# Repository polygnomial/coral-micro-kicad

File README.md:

# Google Coral Micro KiCad files

- use altium2kicad to convert
- fix certain text fields
- fix schematic libraries
- link schematics hierarchicly
- put all rescued footprints in new footprint library
- delete all the random files

## TODO

- fix STEP files

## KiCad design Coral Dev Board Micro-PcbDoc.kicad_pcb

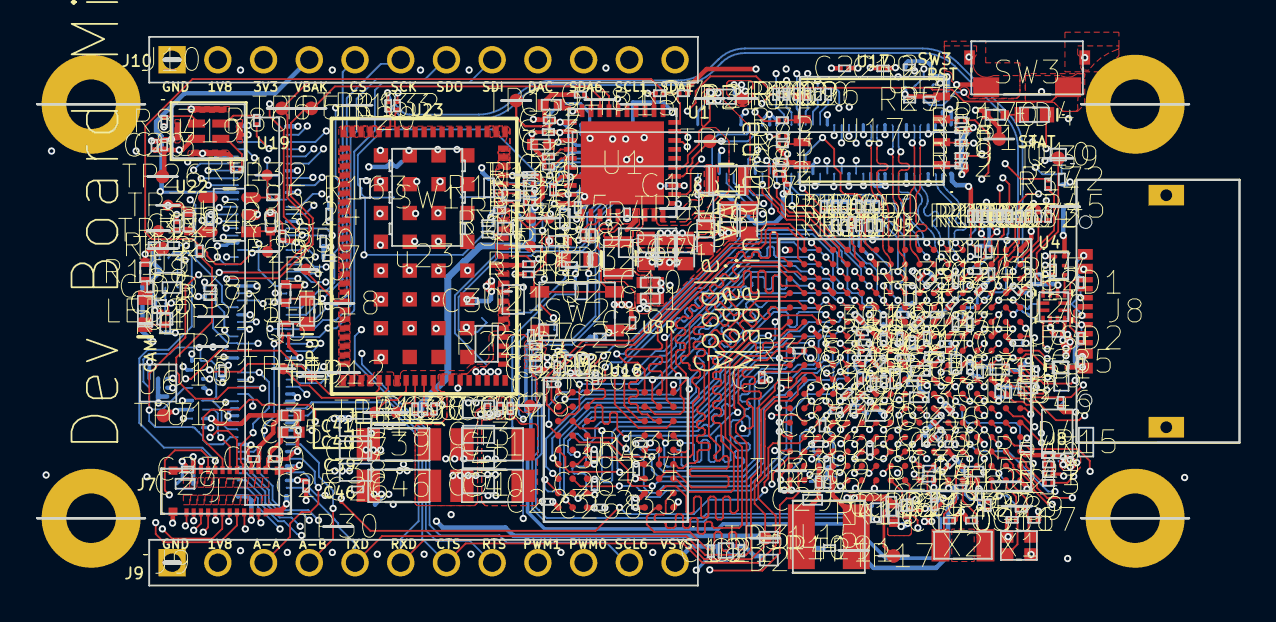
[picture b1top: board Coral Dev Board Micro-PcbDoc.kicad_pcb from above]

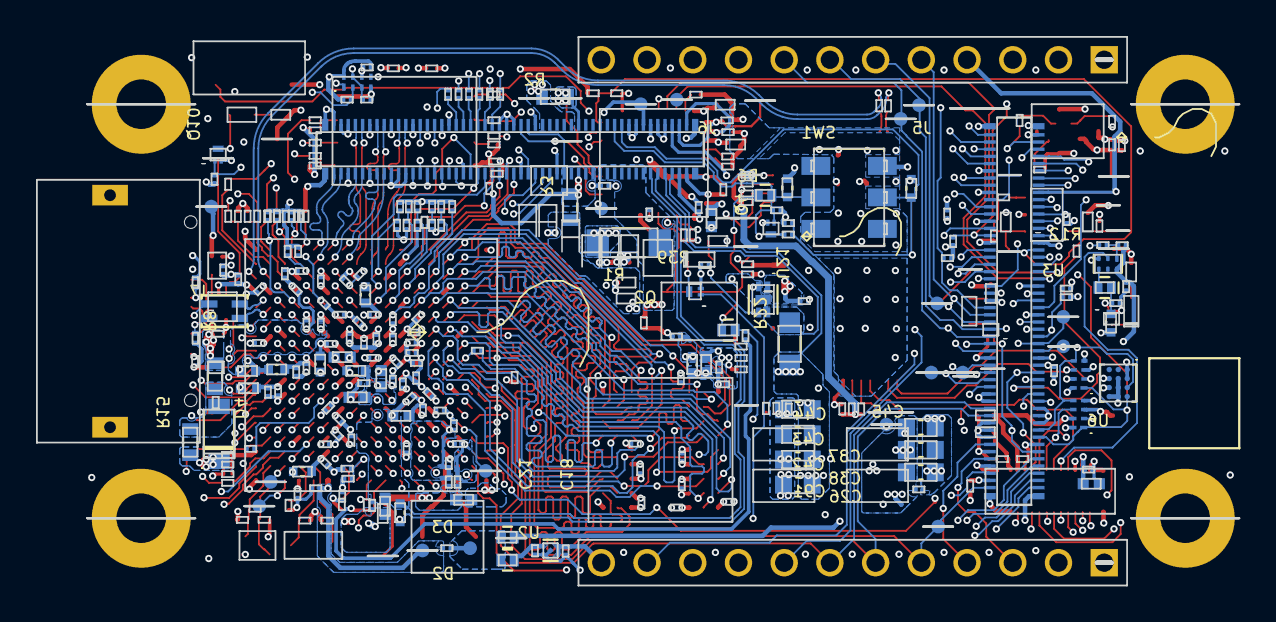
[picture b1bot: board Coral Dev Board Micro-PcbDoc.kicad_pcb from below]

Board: 8 copper layers, 66.8 x 30.5 mm, 356 parts (200 on the bottom side), 316 nets.

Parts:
C1: C1; C0201_MOD
C2: C2; C0402
C3: C3; C0402
C4: C4; C0603_L_ZEROMASK
C5: C5; C0603_L_ZEROMASK
C6: C6; C0603_L_ZEROMASK
C7: C7; C0603_L_ZEROMASK
C8: C8; C0603_L_ZEROMASK
C9: C9; C0603_L_ZEROMASK
C10: C10; C0402
C11: C11; C0402
C12: C12; C0201_MOD
C13: C13; C0201_MOD
C14: C14; C0201_MOD
C15: C15; C0201_MOD
C16: C16; C0201_MOD
C17: C17; C0201_MOD
C18: C18; C0201_MOD
C19: C19; C0201_MOD
C20: C20; C0201_MOD
C21: C21; C0201_MOD
C22: C22; C0201_MOD
C23: C23; C0201_MOD
C24: C24; C0201_MOD
C25: C25; C0201_MOD
C26: C26; C0201_MOD
C27: C27; C0201_MOD
C28: C28; C0201_MOD
C29: C29; C0402
C30: C30; C0201_MOD
C31: C31; C0402
C32: C32; C0402
C33: C33; C0201_MOD
C34: C34; C0201_MOD
C35: C35; C0402
C36: C36; C0201_MOD
C37: C37; C0201_MOD
C38: C38; C0603
C39: C39; C1206Y_1.90MM
C40: C40; C1206Y_1.90MM
C41: C41; C1206Y_1.90MM
C42: C42; C0603
C43: C43; C0603
C44: C44; C0603
C45: C45; C0603
C46: C46; C1206Y_1.90MM
C57: C57; C0201_MOD
C61: C61; C0402
C62: C62; C0201_MOD
C63: C63; C0402
C67: C67; C0201_MOD
C74: C74; C0402
C79: C79; C0201_MOD
C80: C80; C0201_MOD
C81: C81; C0201_MOD
C82: C82; C0201_MOD
C83: C83; C0201_MOD
C84: C84; C0201_MOD
C85: C85; C0201_MOD
C87: C87; C0603
C88: C88; C0201_MOD
C90: C90; C0201_MOD
C91: C91; C0603
C92: C92; C0201_MOD
C93: C93; C0201_MOD
C94: C94; C0201_MOD
C95: C95; C0201_MOD
C96: C96; C0201_MOD
C97: C97; C0201_MOD
C98: C98; C0201_MOD
C102: C102; C0201_MOD
C107: C107; C0201_MOD
C109: C109; C0201_MOD
C110: C110; C0201_MOD
C115: C115; C0201_MOD
C117: C117; C0201_MOD
C118: C118; C0402
C119: C119; C0201_MOD
C124: C124; C0201_MOD
C136: C136; C0201_MOD
C138: C138; C0402
C223: C223; C0201_MOD
C224: C224; C0201_MOD
C233: C233; C0201_MOD
C234: C234; C0201_MOD
C235: C235; C0201_MOD
C239: C239; C0201_MOD
C241: C241; C0201_MOD
C242: C242; C0201_MOD
C244: C244; C0201_MOD
C245: C245; C0201_MOD
C251: C251; C0201_MOD
C252: C252; C0201_MOD
C254: C254; C0201_MOD
C256: C256; C0201_MOD
C257: C257; C0201_MOD
C258: C258; C0201_MOD
C260: C260; C0201_MOD
C261: C261; C0201_MOD
C264: C264; C0201_MOD
C265: C265; C0201_MOD
C266: C266; C0201_MOD
C267: C267; C0201_MOD
C268: C268; C0201_MOD
C269: C269; C0201_MOD
C270: C270; C0201_MOD
C272: C272; C0201_MOD
C273: C273; C0201_MOD
C276: C276; C0201_MOD
C277: C277; C0201_MOD
C279: C279; C0201_MOD
C280: C280; C0201_MOD
C285: C285; C0201_MOD
C286: C286; C0201_MOD
C287: C287; C0201_MOD
C290: C290; C0201_MOD
C293: C293; C0201_MOD
C294: C294; C0402
C296: C296; C0201_MOD
C297: C297; C0402
C300: C300; C0201_MOD
C302: C302; C0201_MOD
C303: C303; C0201_MOD
C304: C304; C0201_MOD
C305: C305; C0201_MOD
C316: C316; C0201_MOD
C317: C317; C0201_MOD
C327: C327; C0201_MOD
C345: C345; C0201_MOD
C347: C347; C0201_MOD
C348: C348; C0201_MOD
D1: D1; D0402_H0.55MM
D2: D2; D0402_H0.55MM
D3: D3; D0402_H0.55MM
D4: D4; SOD123_AK
D5: D5; D0402_H0.55MM
D6: D6; D0402_H0.55MM
D31: D31; SOD1060X40
ESD1: ESD1; 0201
ESD2: ESD2; 0201
FB1: FB1; L0402_H0.55MM
FB2: FB2; L0402_H0.55MM
FB3: FB3; L0402_H0.55MM
FB4: FB4; L0402_H0.55MM
FB5: FB5; L0402_H0.55MM
FB6: FB6; L0402_H0.55MM
J5: J5; HIROSE_DF40C-100DP-0.4V(51)
J6: J6; HIROSE_DF40C-100DP-0.4V(51)
J7: J7; Molex_5037722410_HM01B0
J8: J8; EDAC_698B116W26A-661
J9: J9; HEADER_1X12_POS_UNSHROUDED
J10: J10; HEADER_1X12_POS_UNSHROUDED
L1: L1; L2016_H1.0MM
L2: L2; L2016_H1.0MM
L7: L7; IND4_CHOKE_0805
L15: L15; IND_74404041047
LED2: LED2; LED_0603_0.67mm
LED3: LED3; LED_0603_0.67mm
LED4: LED4; LED_0603P_ORANGE
LED5: LED5; LED_0603P_WHITE
Q1: Q1; 3XDFN
Q2: Q2; 3XDFN
Q3: Q3; 3XDFN
Q4: Q4; 3XDFN
Q10: Q10; 3XDFN
R1: R1; R1206
R2: R2; R0603
R3: R3; R0603
R4: R4; R0201_MOD
R5: R5; R0201_MOD
R6: R6; R0201_MOD
R7: R7; R0201_MOD
R8: R8; R0603
R9: R9; R0201_MOD
R10: R10; R0201_MOD
R11: R11; R0402
R12: R12; R0201_MOD
R13: R13; R0201_MOD
R14: R14; R0201_MOD
R15: R15; R0603
R16: R16; R0201_MOD
R17: R17; R0201_MOD
R18: R18; R0201_MOD
R19: R19; R0201_MOD
R20: R20; R0201_MOD
R21: R21; R0201_MOD
R22: R22; R0805
R23: R23; R0201_MOD
R24: R24; R0201_MOD
R26: R26; R0201_MOD
R27: R27; R0201_MOD
R29: R29; R0201_MOD
R30: R30; R0201_MOD
R31: R31; R0201_MOD
R32: R32; R0201_MOD
R33: R33; R0201_MOD
R34: R34; R0201_MOD
R35: R35; R0201_MOD
R36: R36; R0201_MOD
R37: R37; R0201_MOD
R38: R38; R0201_MOD
R39: R39; R0201_MOD
R40: R40; R0201_MOD
R41: R41; R0201_MOD
R43: R43; R0201_MOD
R44: R44; R0201_MOD
R45: R45; R0201_MOD
R46: R46; R0201_MOD
R47: R47; R0201_MOD
R48: R48; R0201_MOD
R49: R49; R0201_MOD
R50: R50; R0201_MOD
R51: R51; R0201_MOD
R53: R53; R0201_MOD
R71: R71; R0201_MOD
R72: R72; R0201_MOD
R73: R73; R0201_MOD
R74: R74; R0201_MOD
R75: R75; R0201_MOD
R76: R76; R0201_MOD
R78: R78; R0201_MOD
R79: R79; R0201_MOD
R84: R84; R0201_MOD
R85: R85; R0201_MOD
R86: R86; R0201_MOD
R87: R87; R0201_MOD
R90: R90; R0201_MOD
R91: R91; R0201_MOD
R93: R93; R0402
R95: R95; R0201_MOD
R99: R99; R0402
R110: R110; R0201_MOD
R116: R116; R0201_MOD
R117: R117; R0402
R125: R125; R0201_MOD
R129: R129; R0201_MOD
R132: R132; R0201_MOD
R133: R133; R0201_MOD
R135: R135; R0201_MOD
R136: R136; R0201_MOD
R137: R137; R0201_MOD
R138: R138; R0201_MOD
R139: R139; R0201_MOD
R140: R140; R0201_MOD
R141: R141; R0201_MOD
R142: R142; R0201_MOD
R143: R143; R0201_MOD
R144: R144; R0201_MOD
R145: R145; R0201_MOD
R146: R146; R0201_MOD
R147: R147; R0201_MOD
R148: R148; R0201_MOD
R149: R149; R0201_MOD
R150: R150; R0201_MOD
R151: R151; R0201_MOD
R152: R152; R0201_MOD
R153: R153; R0201_MOD
R154: R154; R0201_MOD
R155: R155; R0201_MOD
R156: R156; R0201_MOD
R157: R157; R0201_MOD
R158: R158; R0201_MOD
R159: R159; R0201_MOD
R160: R160; R0201_MOD
R161: R161; R0201_MOD
R162: R162; R0201_MOD
R163: R163; R0402
R164: R164; R0402
R166: R166; R0201_MOD
R167: R167; R0201_MOD
R168: R168; R0402
R169: R169; R0402
R170: R170; R0402
R171: R171; R0402
R172: R172; R0201_MOD
R189: R189; R0201_MOD
R194: R194; R0402
R215: R215; R0201_MOD
R365: R365; R0201_MOD
R373: R373; R0201_MOD
R374: R374; R0201_MOD
R375: R375; R0201_MOD
R396: R396; R0201_MOD
R397: R397; R0201_MOD
R398: R398; R0201_MOD
R415: R415; R0402
R416: R416; R0402
R419: R419; R0201_MOD
R1821: R1821; R0201_MOD
R1848: R1848; R0201_MOD
SW1: SW1; SWITCH_CAS-D20TA
SW2: SW2; SWITCH_TAH1QR
SW3: SW3; SWITCH_TL4100AF120QG
TP1: TP1; TESTPAD_SMT_30MIL
TP2: TP2; TESTPAD_SMT_30MIL
TP3: TP3; TESTPAD_SMT_30MIL
TP4: TP4; TESTPAD_SMT_30MIL
TP5: TP5; TESTPAD_SMT_30MIL
TP6: TP6; TESTPAD_SMT_30MIL
TP7: TP7; TESTPAD_SMT_30MIL
TP8: TP8; TESTPAD_SMT_30MIL
TP9: TP9; TESTPAD_SMT_30MIL
TP10: TP10; TESTPAD_SMT_30MIL
TP11: TP11; TESTPAD_SMT_30MIL
TP12: TP12; TESTPAD_SMT_30MIL
TP13: TP13; TESTPAD_SMT_30MIL
TP14: TP14; TESTPAD_SMT_30MIL
TP15: TP15; TESTPAD_SMT_30MIL
TP16: TP16; TESTPAD_SMT_30MIL
TP17: TP17; TESTPAD_SMT_30MIL
TP18: TP18; TESTPAD_SMT_30MIL
TP19: TP19; TESTPAD_SMT_30MIL
TP20: TP20; TESTPAD_SMT_30MIL
TP21: TP21; TESTPAD_SMT_30MIL
TP22: TP22; TESTPAD_SMT_30MIL
TP23: TP23; TESTPAD_SMT_30MIL
TP24: TP24; TESTPAD_SMT_30MIL
TP25: TP25; TESTPAD_SMT_30MIL
TP26: TP26; TESTPAD_SMT_30MIL
TP27: TP27; TESTPAD_SMT_30MIL
TP28: TP28; TESTPAD_SMT_25MIL
TP29: TP29; TESTPAD_SMT_25MIL
TP30: TP30; TESTPAD_SMT_30MIL
TP31: TP31; TESTPAD_SMT_30MIL
TP32: TP32; TESTPAD_SMT_25MIL
TP33: TP33; TESTPAD_SMT_25MIL
TP34: TP34; TESTPAD_SMT_25MIL
TP35: TP35; TESTPAD_SMT_25MIL
TP36: TP36; TESTPAD_SMT_25MIL
TP37: TP37; TESTPAD_SMT_25MIL
TP38: TP38; TESTPAD_SMT_25MIL
TP39: TP39; TESTPAD_SMT_30MIL
TP40: TP40; TESTPAD_SMT_25MIL
TP41: TP41; TESTPAD_SMT_25MIL
TP42: TP42; TESTPAD_SMT_25MIL
TP43: TP43; TESTPAD_SMT_25MIL
TP44: TP44; TESTPAD_SMT_25MIL
TP45: TP45; TESTPAD_SMT_30MIL
U1: U1; QFN50P600X600X90-40-TP
U2: U2; SDFN80X80X40-5
U3: U3; SON50P145X100X60-6
U4: U4; SON50P145X100X50-6
U5: U5; BGA289C80P17X17_1400X14000X152
U6: U6; BGA12C50+3X4_206X202X65
U10: U10; SON8_0P5_1L95x1W
U13: U13; SON8_0P5_1L95x1W
U14: U14; SON8_0P5_1L95x1W
U17: U17; UDFN800X600X65-8
U18: U18; BGA54C80P6X9_800X800X100
U19: U19; MIC_SPK0641HT4H-1
U20: U20; X2QFN12_1.6X1.6MMM
U21: U21; TDFN120X160X60-4-TP
U22: U22; 5SOT23_REG
X1: X1; XTAL_MURATA_XRCGB24M000F1H01R0
X2: X2; XTAL_EPSON_ADUCM355BCCZ
u23: u23; QFN120_0P5_10X15

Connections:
ADC1_CH0A: J5.10, J9.3, U5.N13
ADC1_CH0B: J5.14, J9.4, U5.T17
ADC1_CH2A: C33.1, R40.1, R41.2, U5.R17
ADC1_CH2B: J5.6, U5.P16
ADC_1V8_IN: C117.1, C136.1, C347.1, C348.1, FB2.2, U5.G16, U5.K15, U5.M11
BOOT_MODE0: J6.19, R30.1, R31.2, R163.2, SW1.5, U5.P6
BOOT_MODE1: D6.A, J6.21, Q4.1, R29.1, R164.2, SW1.2, U5.T7
BRD_STAT_LED: J5.80, Q10.1, R172.1, U5.L9
BT_CFG1_0_ENET_RGMII_TXD3: R10.2, R139.1, R151.1, U5.D10
BT_CFG1_1_ENET_RGMII_TXD2: R16.2, R140.1, R152.1, U5.E12
BT_CFG1_2_ENET_RGMII_TXD1: R18.2, R141.1, R153.1, U5.A15
BT_CFG1_3_ENET_RGMII_TXD0: R19.2, R142.1, R154.1, U5.C13
BT_CFG1_4_ENET_RGMII_TX_EN: R20.2, R143.1, R155.1, U5.B14
BT_CFG1_5_ENET_RGMII_TXC: R26.2, R144.1, R156.1, U5.A14
BT_CFG1_6: R145.1, R157.1, U5.E8
BT_CFG1_7: R146.1, R158.1, U5.F8
BT_CFG2_0: R147.1, R159.1, U5.E9
BT_CFG2_1: R148.1, R160.1, U5.D7
BT_CFG2_2: R149.1, R161.1, U5.C7
BT_CFG2_3: R150.1, R162.1, U5.C9
BT_CFG_IO_EN: R27.2, U5.P13, U14.3, U14.7
BT_DEV_WAKE: J6.62, U5.A7
BT_HOST_WAKE: J6.50, U5.A4
BT_REG_ON: J5.87, U5.G17
BUCK2_SW: L1.1, U1.20
BUCK3_SW: L2.1, U1.17
CAMERA_INT: J5.33, J7.9, U5.P9
CAMERA_TRIG: J7.4, U5.T2
CON_DET: TP39.1, U20.5
CRYPTO_RST_N: U5.U8, U6.C3
CSI_DATA02: J7.17, U5.J12
CSI_DATA03: J7.18, U5.K12
CSI_DATA04: J7.19, U5.K14
CSI_DATA05: J7.20, U5.K13
CSI_DATA06: J7.21, U5.L16
CSI_DATA07: J7.22, U5.M16
CSI_DATA08: J7.23, U5.N15
CSI_DATA09: J7.24, U5.N17
CSI_HSYNC: J7.6, U5.M14
CSI_MCLK: J7.14, R44.2
CSI_MCLK_RT: R44.1, U5.L12
CSI_PIXCLK: J7.16, U5.P17
CSI_VSYNC: J7.5, U3.2, U5.N14
DAC_OUT: D31.K, J5.95, J10.9, U5.H16
DA_GPIO0_WDOG_KICK: J5.55, TP27.1, U1.21, U5.P10
DA_GPIO2: J5.63, U1.28
DA_GPIO3: J5.65, U1.29
DA_GPIO4_SYS_EN: J5.67, R6.2, R7.1, R9.2, U1.30
DA_IREF: R5.2, U1.4
DA_VDDCORE: C1.2, U1.39
DA_VREF: C16.1, U1.5
DA_nIRQ: J5.61, TP6.1, U1.37
DA_nONKEY: D1.K, D6.K, R166.1, SW2.1, SW2.2, U1.15
DA_nRESET: J5.59, TP5.1, U1.38
DA_nRESETREQ: J5.74, R4.1, U1.16
DCDC_1V8_OUT: C19.1, C22.1, C279.1, FB2.1, J6.10, R7.2, R23.2, R24.2, R139.2, R140.2, R141.2, R142.2, R143.2, R144.2, R145.2, R146.2, R147.2, R148.2, R149.2, R150.2, R373.2, R374.2, R416.2, SW1.4, U5.M6
DCDC_1V8_OUT_SENSE: C118.1, C124.1, C138.1, C280.1, J6.12, R416.1, U5.M7, U5.M8
DCDC_PSWITCH: C286.1, R396.2, U5.P3
DMIC_DATA0: J5.45, R87.2, U5.R6
DMIC_DATA0_ONBOARD: R87.1, U19.1
DMIC_DATA1: J5.43, R37.1, R38.2, U5.U6
DMIC_DATA2__JTAG_TCK: J5.41, TP21.1, U5.T6
DMIC_DATA3__JTAG_TMS: J5.39, TP24.1, U5.U7
DVDD15: C35.1, C80.1, J7.12
ENET_RGMII_MDC: J6.44, U5.U2
ENET_RGMII_MDIO: J6.46, U5.R3
ENET_RGMII_RXC: J6.78, U5.D13
ENET_RGMII_RXD0: J6.70, U5.D11
ENET_RGMII_RXD1: J6.68, U5.E11
ENET_RGMII_RXD2: J6.66, U5.E10
ENET_RGMII_RXD3: J6.72, U5.C11
ENET_RGMII_RX_EN: J6.76, U5.E13
ENET_RGMII_TXC: J6.65, R26.1
ENET_RGMII_TXD0: J6.61, R19.1
ENET_RGMII_TXD1: J6.59, R18.1
ENET_RGMII_TXD2: J6.57, R16.1
ENET_RGMII_TXD3: J6.55, R10.1
ENET_RGMII_TX_EN: J6.63, R20.1
ETHPHY_RST_B: J6.42, U5.R1
FLEXPWM1_PWM0_A: J5.9, J9.10, U5.N12
FLEXPWM1_PWM0_B: J5.7, J9.9, U5.R14
FLEXPWM1_PWM1_A: J5.11, Q3.1, U5.R13
FLEXPWM1_PWM1_B: J5.5, U5.P15
FLEXPWM2_PWM1_A: J5.3, U5.L14
FLEXPWM2_PWM1_B: J5.1, U5.N16
Flash_CS: R72.1, R79.2, U17.1
Flash_D0: R76.2, U17.5
Flash_D1: R78.2, U17.2
Flash_D2: R74.1, R85.2, U17.3
Flash_D3: R73.1, R84.2, U17.7
Flash_SCK: R75.2, U17.6
FlexSPI_A_CLK: R75.1, U5.G14
FlexSPI_A_D0: R76.1, U5.F15
FlexSPI_A_D1: R78.1, U5.H15
FlexSPI_A_D2: R85.1, U5.H14
FlexSPI_A_D3: R84.1, U5.F16
FlexSPI_A_SS0: R79.1, U5.F17
GND: C1.1, C2.2, C3.2, C4.2, C5.2, C6.2, C7.2, C8.2, C9.2, C10.2, C11.2, C12.2, C13.2, C14.2, C15.2, C16.2, C17.2, C18.2, C19.2, C20.2, C21.2, C22.2, C23.2, C24.2, C25.2, C26.2, C27.2, C28.2, C29.2, C30.2, C31.2, C32.2, C33.2, C34.2, C35.2, C36.2, C37.2, C38.2, C39.2, C40.2, C41.2, C42.2, C43.2, C44.2, C45.2, C46.2, C57.2, C61.2, C62.2, C63.2, C67.2, C74.2, C79.2, C80.2, C81.2, C82.2, C83.2, C84.2, C85.2, C87.2, C88.2, C90.2, C91.2, C92.2, C93.2, C94.2, C95.2, C96.2, C97.2, C98.2, C102.2, C107.2, C109.2, C110.2, C115.2, C117.2, C118.2, C119.2, C124.2, C136.2, C138.2, C223.2, C224.2, C233.2, C234.2, C235.2, C239.2, C241.2, C242.2, C244.2, C245.2, C251.2, C252.2, C254.2, C256.2, C257.2, C258.2, C260.2, C261.2, C264.2, C265.2, C266.2, C267.2, C268.2, C269.2, C270.2, C272.2, C273.2, C276.2, C277.2, C279.2, C280.2, C285.2, C286.2, C287.2, C290.2, C293.2, C294.2, C296.2, C297.2, C300.2, C302.2, C303.2, C304.2, C305.2, C316.1, C317.2, C327.2, C345.2, C347.2, C348.2, D31.A, ESD1.1, ESD2.1, J5.4, J5.8, J5.12, J5.13, J5.16, J5.18, J5.19, J5.20, J5.21, J5.23, J5.26, J5.28, J5.37, J5.38, J5.49, J5.54, J5.57, J5.69, J5.70, J5.76, J5.84, J5.90, J5.99, J5.MH1, J5.MH2, J5.MH3, J5.MH4, J6.7, J6.9, J6.11, J6.15, J6.17, J6.38, J6.43, J6.48, J6.49, J6.51, J6.53, J6.64, J6.67, J6.74, J6.77, J6.80, J6.82, J6.83, J6.84, J6.89, J6.90, J6.95, J6.96, J6.97, J6.99, J6.MH1, J6.MH2, J6.MH3, J6.MH4, J7.1, J7.3, J7.10, J7.13, J7.15, J7.MH1, J7.MH2, J7.MH3, J7.MH4, J8.1, J8.12, J8.SH1, J8.SH2, J9.1, J10.1, Q1.2, Q2.2, Q3.2, Q4.2, Q10.2, R5.1, R9.1, R11.1, R14.2, R17.1, R27.1, R38.1, R39.1, R41.1, R91.1, R125.1, R129.1, R135.1, R136.1, R151.2, R152.2, R153.2, R154.2, R155.2, R156.2, R157.2, R158.2, R159.2, R160.2, R161.2, R162.2, R163.1, R164.1, R398.1, SW1.3, SW1.6, SW2.3, SW2.4, SW3.2, SW3.SH, U1.7, U1.32, U1.41, U2.2, U2.5, U3.3, U4.3, U5.A1, U5.A17, U5.B7, U5.C8, U5.C10, U5.C12, U5.C14, U5.D4, U5.F11, U5.F12, U5.F13, U5.G3, U5.G7, U5.G8, U5.G9, U5.G10, U5.G11, U5.G15, U5.H7, U5.H11, U5.J7, U5.J11, U5.K6, U5.K7, U5.K11, U5.L3, U5.L6, U5.L10, U5.L11, U5.L15, U5.P4, U5.P14, U5.R4, U5.R7, U5.T12, U5.U1, U5.U17, U6.A1, U6.A2, U6.C2, U10.4, U13.4, U14.4, U17.4, U18.A1, U18.A3, U18.B7, U18.C3, U18.D7, U18.E3, U18.J1, U19.5, U19.6, U19.7, U19.8, U20.10, U21.2, U21.5, U22.2, X1.2, X1.4, u23.1, u23.2, u23.3, u23.6, u23.7, u23.8, u23.9, u23.10, u23.11, u23.12, u23.15, u23.16, u23.17, u23.18, u23.19, u23.20, u23.21, u23.22, u23.23, u23.24, u23.25, u23.26, u23.27, u23.28, u23.29, u23.30, u23.31, u23.32, u23.33, u23.34, u23.35, u23.36, u23.38, u23.39, u23.40, u23.41, u23.42, u23.43, u23.44, u23.45, u23.46, u23.47, u23.48, u23.51, u23.55, u23.68, u23.69, u23.70, u23.71, u23.72, u23.73, u23.74, u23.75, u23.79, u23.80, u23.81, u23.86, u23.87, u23.88, u23.89, u23.90, u23.91, u23.92, u23.93, u23.94, u23.95, u23.96, u23.97, u23.98, u23.99, u23.100, u23.101, u23.102, u23.103, u23.104, u23.105, u23.106, u23.107, u23.108, u23.109, u23.110, u23.111, u23.112, u23.113, u23.114, u23.115, u23.116, u23.117, u23.118, u23.119, u23.120
GPIO_SNVS_04: J5.58, U5.N10
GPIO_SNVS_06: J5.78, U5.M9
GPIO_SNVS_07: J5.34, U5.R9
GPIO_SNVS_08: J5.56, U5.N9
I2C1_SCL: J5.51, J10.11, R46.1, U5.K16
I2C1_SDA: J5.52, J10.12, R47.1, U5.H17
I2C5_SCL: J5.17, R49.1, U1.14, U5.N8, U6.A3, U10.5, U13.5
I2C5_SCL_CAM: J7.7, U13.6
I2C5_SCL_MCM: TP41.1, U10.6, u23.50
I2C5_SDA: J5.15, R48.1, U1.13, U5.N7, U6.A4, U10.1, U13.1
I2C5_SDA_CAM: J7.8, U13.2
I2C5_SDA_MCM: TP42.1, U10.2, u23.49
I2C6_SCL: J5.35, J9.11, R51.1, U5.R8
I2C6_SDA: J5.72, J10.10, R50.1, U5.P8
LED_BRD_A: LED4.2, R170.1
LED_BRD_K: LED4.1, Q10.3
LED_PRIVACY: LED2.A, R168.1
LED_PRIVACY_K: LED2.K, Q1.3
LED_TPU: LED5.2, R171.1
LED_TPU_K: LED5.1, Q3.3
LED_USR_A: LED3.A, R169.1
LED_USR_K: LED3.K, Q2.3
LPSPI1_PCS0: J6.71, U5.M17
LPSPI1_SCK: J6.69, U5.L17
LPSPI1_SDI: J6.75, U5.J17
LPSPI1_SDO: J6.73, U5.K17
LPSPI6_CS0: J5.50, J10.5, U5.P5
LPUART1_RXD: J5.91, U14.5
LPUART1_RXD_BT: R21.1, U5.M15, U14.6
LPUART1_TXD: J5.89, U14.1
LPUART1_TXD_BT: R53.1, U5.L13, U14.2
LPUART2_CTS_B: J6.56, R45.2
LPUART2_CTS_B_R: R45.1, U5.B6
LPUART2_RTS_B: J6.54, U5.A5
LPUART2_RXD: J6.60, U5.A6
LPUART2_TXD: J6.58, U5.D9
LPUART6_CTS_B: J5.24, J9.7, U5.K2
LPUART6_RTS_B: J5.47, J9.8, U5.K4
LPUART6_RXD: J5.22, J9.6, TP31.1, U5.L1
LPUART6_TXD: J5.2, J9.5, TP30.1, U5.K1
LPUART8_RXD: J5.82, U5.D8
LPUART8_TXD: J6.52, U5.B5
MCM_1V8: C98.1, R99.2, R110.2, R116.2, R137.2, R138.2, TP34.1, U5.P2, U10.3, U10.7
MCM_1V8_R: C92.1, R99.1, TP33.1, U22.5
MCM_3V3: C39.1, C40.1, C41.1, C42.1, C43.1, C44.1, C46.1, C90.1, C91.1, C93.1, C94.1, C95.1, C96.1, C97.1, C251.1, J6.6, R22.2, R93.1, R171.2, TP28.1, U5.D16, u23.56, u23.57, u23.58, u23.59, u23.60, u23.61, u23.62, u23.63, u23.64, u23.65, u23.66, u23.67
MCM_3V3_SENSE: J6.8, R22.1, U21.4
MCM_AON: R137.1, u23.54
MCM_AON_PMIC_EN: R138.1, TP43.1, u23.53
MCM_BT_PHY_PRG: R116.1, R129.2, TP35.1, u23.84
MCM_LDO_EN: R95.1, TP32.1, U22.3
MCM_LDO_IN: C88.1, R93.2, R95.2, TP29.1, U22.1
MCM_SD_ALARM: TP37.1, U5.L4, u23.82
MCM_USB2_D_N: R133.2, u23.14
MCM_USB2_D_P: R132.2, u23.13
MCM_USB_SEL: R110.1, R125.2, TP36.1, u23.83
MCU_DCDC_IN: C102.1, C277.1, C294.1, R194.2, R396.1, R397.1, TP17.1, U5.L5, U5.M5, U5.N5
MIC_CH_SEL: R91.2, U19.3
MIC_CLK: J5.97, R86.1, U5.N6
MIC_CLK_R: R86.2, U19.2
MIPI_CSI_CK_N: J6.94, U5.A12
MIPI_CSI_CK_P: J6.92, U5.B12
MIPI_CSI_D0_N: J6.88, U5.A11
MIPI_CSI_D0_P: J6.86, U5.B11
MIPI_CSI_D1_N: J6.100, U5.A13
MIPI_CSI_D1_P: J6.98, U5.B13
MIPI_DSI_CK_N: J6.87, U5.A9
MIPI_DSI_CK_P: J6.85, U5.B9
MIPI_DSI_D0_N: J6.81, U5.A8
MIPI_DSI_D0_P: J6.79, U5.B8
MIPI_DSI_D1_N: J6.93, U5.A10
MIPI_DSI_D1_P: J6.91, U5.B10
NetC34_1: C34.1, U5.J2
NetC57_1: C57.1, C63.1, C74.1, C269.1, R117.1, U5.K8, U5.K9, U5.L8
NetC242_1: C242.1, R375.2, U5.D14
NetQ4_3: Q4.3, R31.1
NetR12_1: R12.1, R13.1, U3.1
NetTP8_1: TP8.1, U1.36
NetTP40_1: TP40.1, u23.37
NetTP44_1: TP44.1, u23.52
ONOFF: J5.30, U5.U10
OTG1_D_N: L7.2, U5.E16
OTG1_D_P: L7.3, U5.E17
PMIC_ON_REQ: J5.29, R6.1, R1821.1, TP13.1, U5.U9
PMIC_STBY_REQ: J5.32, TP12.1, U5.T9
POR_B: C115.1, J5.60, R215.1, SW3.1, U1.22, U5.T10
PRIVACY_ENABLE: D5.A, U3.4
PRIVACY_ENABLE_FILT: C36.1, D5.K, Q1.1, R11.2
PRIVACY_OVERRIDE: R12.2, U5.M2
QSPI_1V8: C81.1, C82.1, R71.1, R72.2, R73.2, R74.2, U17.8
RGMII1_PHY_INTB: J6.40, U5.K3
RTC_XTALI: C110.1, U5.T13, X2.1
RTC_XTALO: C109.1, U5.U13, X2.2
RT_CLK1_N: TP22.1, U5.T15
RT_CLK1_P: TP23.1, U5.U15
RT_DCDC_L_1: L15.1, U5.T3, U5.U3
RT_DCDC_L_2: L15.2, U5.T4, U5.U4
RT_DCDC_MODE: C287.1, R397.2, R398.2, U5.N4
RT_TEST_MODE: R14.1, U5.T11
RT_XTALI: C316.2, R189.2, U5.U16, X1.1
RT_XTALO: C317.1, R189.1, U5.T16, X1.3
SAI2_MCLK: J5.66, U5.M1
SAI2_RX_BCLK: J5.42, U5.T1
SAI2_RX_DATA: J5.68, U5.M3
SAI2_RX_SYNC: J5.62, U5.N1
SAI2_TX_BCLK: J5.64, U5.N2
SAI2_TX_DATA: J5.53, U5.P1
SAI2_TX_SYNC: J5.40, U5.R2
SDRAM_1V8: C223.1, C224.1, C233.1, C234.1, C267.1, C268.1, C297.1, C303.1, C304.1, FB6.2, R90.2, U18.A7, U18.A9, U18.B3, U18.C7, U18.D3, U18.E7, U18.J9
SEMC_A0: U5.A3, U18.H7
SEMC_A1: U5.A2, U18.H8
SEMC_A2: U5.C2, U18.J8
SEMC_A3: U5.C5, U18.J7
SEMC_A4: U5.D5, U18.J3
SEMC_A5: U5.B1, U18.J2
SEMC_A6: U5.C1, U18.H3
SEMC_A7: U5.D3, U18.H2
SEMC_A8: U5.B3, U18.H1
SEMC_A9: U5.B4, U18.G3
SEMC_A10: U5.B2, U18.H9
SEMC_A11: U5.C4, U18.G2
SEMC_A12: U5.C3, U18.G1
SEMC_BA0: U5.G2, U18.G7
SEMC_BA1: U5.H2, U18.G8
SEMC_CAS: U5.J5, U18.F7
SEMC_CKE: R135.2, U5.G5, U18.F3
SEMC_CLK: R365.1, U5.J3
SEMC_CLK_R: R365.2, U18.F2
SEMC_CS0: R90.1, U5.E6, U18.G9
SEMC_D0: U5.F3, U18.A8
SEMC_D1: U5.F2, U18.B9
SEMC_D2: U5.G4, U18.B8
SEMC_D3: U5.E4, U18.C9
SEMC_D4: U5.H5, U18.C8
SEMC_D5: U5.F4, U18.D9
SEMC_D6: U5.H4, U18.D8
SEMC_D7: U5.H3, U18.E9
SEMC_D8: U5.E3, U18.E1
SEMC_D9: U5.D2, U18.D2
SEMC_D10: U5.D1, U18.D1
SEMC_D11: U5.E2, U18.C2
SEMC_D12: U5.E1, U18.C1
SEMC_D13: U5.F1, U18.B2
SEMC_D14: U5.G1, U18.B1
SEMC_D15: U5.H1, U18.A2
SEMC_DM0: U5.F5, U18.E8
SEMC_DM1: U5.J1, U18.F1
SEMC_DQS4: TP25.1, U5.N3
SEMC_RAS: U5.J4, U18.F8
SEMC_WE: U5.E5, U18.F9
SPI6_SCK__JTAG_nTRST: J5.48, J10.6, TP18.1, U5.R5
SPI6_SDI__JTAG_TDI: J5.44, J10.8, TP20.1, U5.U5
SPI6_SDO__JTAG_TDO: J5.46, J10.7, TP19.1, U5.T5
TPU_BOOT_FAIL: U5.K5, u23.85
TPU_INTR: TP38.1, u23.77
TPU_POW_EN: R39.2, U5.L2, U21.3
TPU_RST_L: R136.2, U5.M4, u23.76
USB2_TPU_N: R133.1, U5.C16
USB2_TPU_P: R132.1, U5.C17
USB_CC1: J8.4, U20.1
USB_CC2: J8.10, U20.2
USB_DN_CON: ESD2.2, J8.5, J8.7, L7.1
USB_DP_CON: ESD1.2, J8.6, J8.8, L7.4
USB_OTG1_ID: R43.2, U20.9
USB_OTG1_ID_RT: R43.1, U5.R16
USB_PORT: U4.4, U20.3
USB_PORT_RT: R17.2, U4.2, U5.R15
USDHC2_CLK: J5.79, U5.F14
USDHC2_CMD: J5.81, R23.1, U5.E14
USDHC2_DATA0: J5.77, R24.1, U5.E15
USDHC2_DATA1: J5.73, U5.H13
USDHC2_DATA2: J5.75, U5.J14
USDHC2_DATA3: J5.71, U5.J15
USER_BUTTON: D1.A, J5.31, R167.1, U5.R10
USER_LED: J5.25, Q2.1, U5.M10
VDDA_1P0: C276.1, J6.5, R1848.1, U5.N11
VDDA_ADC_3P3: C245.1, C257.1, FB1.1, U5.J13
VDD_1V8: C23.1, C24.1, C25.1, C235.1, C239.1, C241.1, C254.1, C256.1, C258.1, C265.1, C285.1, C327.1, C345.1, FB3.1, FB4.1, FB6.1, J6.28, J6.30, J6.32, J6.34, J6.36, J6.45, J9.2, J10.2, R3.2, R21.2, R29.2, R30.2, R37.2, R46.2, R47.2, R48.2, R49.2, R50.2, R51.2, R53.2, R71.2, R172.2, R375.1, U4.1, U5.D12, U5.E7, U5.F6, U5.F7, U5.G6, U5.G13, U5.H6, U5.J6, U5.M12, U5.P7, U6.B2, U6.B3, U6.B4, U6.C4, U10.8, U13.8, U14.8
VDD_1V8_AON: C12.1, C17.1, J6.3, R166.2, TP1.1, U1.1, U1.23
VDD_1V8_CAM: C14.1, C31.1, C37.1, C79.1, J6.2, J7.11, R13.2, TP7.1, U1.9, U3.6, U13.3, U13.7
VDD_1V8_MIC: C15.1, C20.1, C83.1, J6.4, TP26.1, U1.11, U19.4
VDD_1V8_SENSE: C10.1, C11.1, J6.47, L2.2, R3.1, TP4.1, U1.24
VDD_2V8_CAM: C13.1, C27.1, C29.1, J6.1, J7.2, R168.2, TP2.1, U1.2
VDD_3V3: C2.1, C3.1, C30.1, FB1.2, FB5.1, J6.33, J6.35, J6.37, J6.39, J6.41, J10.3, R2.2, R169.2, R170.2, R194.1, R415.1, TP14.1, TP16.1, U1.3, U1.10, U21.1
VDD_3V3_SENSE: C8.1, C9.1, J6.31, L1.2, R2.1, TP3.1, U1.25
VDD_COIN_3V: D3.A, J5.83, J10.4
VDD_LPSR_ANA: C290.1, U5.P12
VDD_LPSR_DIG: C296.1, U5.P11
VDD_LPSR_IN: C300.1, J6.13, R415.2, TP15.1, U5.R12
VDD_MIPI_1P0: C272.1, R1848.2, U5.F10
VDD_MIPI_1P8: C119.1, FB3.2, U5.F9
VDD_SNVS: C302.1, R419.2, TP11.1, U5.U12
VDD_SNVS_3V3: D2.K, D3.K, R419.1, TP10.1
VDD_SNVS_ANA: C293.1, C305.1, R167.2, R215.2, R1821.2, U5.U11, U5.U14
VDD_SNVS_DIG: C107.1, U5.T14
VDD_SOC_IN: C61.1, C62.1, C67.1, C260.1, C261.1, C264.1, C266.1, C273.1, R117.2, U5.H8, U5.H9, U5.H10, U5.J8, U5.J9, U5.J10, U5.K10, U5.L7
VDD_USB_1P8: C270.1, FB4.2, U5.H12
VDD_USB_3P3: C244.1, FB5.2, U5.G12
VSYS: C18.1, C26.1, C28.1, C38.1, C45.1, C87.1, D4.K, J6.14, J6.16, J6.18, J6.20, J6.22, J6.24, J6.26, J9.12, R1.1, R4.2, R15.1, R40.2, U2.3, U2.4
VSYS_DA: C4.1, C5.1, C6.1, C7.1, C32.1, R1.2, U1.18, U1.19, U1.40
VSYS_SNVS_D: C21.1, D2.A, U2.1
VUSB: C84.1, C85.1, C252.1, J8.2, J8.11, R8.2, TP45.1, U4.6, U5.D17, U20.4, U20.12
VUSB_R: D4.A, R8.1, R15.2
WAKEUP: J5.36, TP9.1, U5.T8
WIFI_POWER_EN: J5.27, U5.R11
WIFI_SDIO_CLK: J5.92, U5.D15
WIFI_SDIO_CMD: J5.100, R32.2
WIFI_SDIO_CMD_R: R32.1, R373.1, U5.B16
WIFI_SDIO_D0: J5.96, R33.2
WIFI_SDIO_D0_R: R33.1, R374.1, U5.C15
WIFI_SDIO_D1: J5.94, R34.2
WIFI_SDIO_D1_R: R34.1, U5.B17
WIFI_SDIO_D2: J5.85, R35.2
WIFI_SDIO_D2_R: R35.1, U5.B15
WIFI_SDIO_D3: J5.98, R36.2
WIFI_SDIO_D3_R: R36.1, U5.A16
WL_ANT_SEL: J5.88, U5.C6
WL_HOST_WAKE: J5.86, U5.D6
WL_REG_ON: J5.93, U5.J16

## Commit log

2024-02-01 fix board
2024-02-01 schematic subdir
2024-02-01 add README
